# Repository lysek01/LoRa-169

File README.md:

# LoRa-169 Gateway Documentation

## Overview
The LoRa-169 Gateway is a Raspberry Pi-based system for receiving and transmitting LoRa packets on the 169 MHz IoT band using the SX127x radio module. It provides MQTT integration for remote control and configuration management.

## System Components

### 1. **lora_gateway.py** - Main Gateway Service
The core application that handles LoRa radio communication and MQTT integration.

**Features:**
- Continuous monitoring for incoming LoRa packets
- MQTT-based packet transmission (hex/ASCII formats)
- Dynamic configuration reloading without restart
- RSSI/SNR measurement and reporting
- Automatic radio recovery on errors

**MQTT Topics:**
- `loravsb/169/rx` - Published when packets are received
- `loravsb/169/tx/hex` - Subscribe to transmit hex-encoded data
- `loravsb/169/tx/ascii` - Subscribe to transmit ASCII data
- `loravsb/169/tx/ack` - Published transmission acknowledgments
- `loravsb/169/config/ack` - Published config change notifications

### 2. **lora_config.py** - Configuration Management Service
Shadow configuration service for remote MQTT-based configuration updates.

**MQTT Topics:**
- `loravsb/169/config/get` - Request current configuration
- `loravsb/169/config/set` - Update configuration (JSON payload)
- `loravsb/169/config/reported` - Reports current configuration state
- `loravsb/169/config/ack` - Configuration operation acknowledgments

### 3. **config.json** - Radio Configuration
LoRa radio parameters (frequency, spreading factor, bandwidth, coding rate, etc.)

### 4. **mqtt.conf** - MQTT Broker Configuration
MQTT connection settings (broker address, port, credentials). Edit this file with your actual broker settings before deployment.

### 5. **install.sh** - Installation Script
Automated setup script that installs dependencies and creates systemd services.

## Radio Configuration Parameters

| Parameter | Value | Description |
|-----------|-------|-------------|
| **frequency** | 169.4375 MHz | Operating frequency (169 MHz IoT band) |
| **spreading_factor** | 12 | SF12 (longest range, slowest speed) |
| **bandwidth** | 41.7 kHz | Narrow bandwidth for 169 MHz |
| **coding_rate** | 5 | 4/5 error correction |
| **ldro_enable** | true | Low Data Rate Optimization |
| **preamble_length** | 8 | 8-symbol preamble |
| **sync_word** | 18 (0x12) | Network sync word |
| **crc_enable** | true | CRC error checking enabled |
| **tx_power** | 30 | 30 dBm output power |
| **rx_gain** | "G1" | Boosted LNA gain mode |

## Error Messages and Status Codes

### Configuration Service Status Codes (lora_config.py)

| Code | Constant | Description | Trigger |
|------|----------|-------------|---------|
| **11** | REPORTED_SENT | Configuration successfully reported | After MQTT connect or GET request |
| **12** | CONFIG_OVERWRITTEN | Configuration file updated | Successful SET operation |
| **13** | CONFIG_APPLIED | New configuration applied to radio | Config change detected |
| **14** | INVALID_PAYLOAD | Malformed JSON received | Invalid/empty JSON in SET message |
| **15** | WRITE_FAILED | File write error | Cannot write config.json |
| **16** | INTERNAL_ERROR | Unhandled exception | Unexpected error in handler |

### Gateway Radio Status Codes (lora_gateway.py)

| Code | Constant | Description |
|------|----------|-------------|
| **0** | STATUS_DEFAULT | Default/idle state |
| **1** | STATUS_TX_WAIT | Waiting for transmission |
| **2** | STATUS_TX_TIMEOUT | Transmission timeout |
| **3** | STATUS_TX_DONE | Transmission completed successfully |
| **4** | STATUS_RX_WAIT | Waiting to receive |
| **5** | STATUS_RX_CONTINUOUS | Continuous receive mode active |
| **6** | STATUS_RX_TIMEOUT | Reception timeout |
| **7** | STATUS_RX_DONE | Packet received successfully |
| **8** | STATUS_HEADER_ERR | LoRa header corruption detected |
| **9** | STATUS_CRC_ERR | CRC checksum validation failed |
| **10** | STATUS_CAD_WAIT | Channel Activity Detection in progress |
| **11** | STATUS_CAD_DETECTED | Channel activity detected |
| **12** | STATUS_CAD_DONE | CAD completed |

### Error Messages

| Error Message | Location | Meaning | Resolution |
|---------------|----------|---------|------------|
| "Invalid JSON payload" | lora_config.py:103 | SET message contains non-JSON data | Send valid JSON object |
| "Write failed" | lora_config.py:112 | Cannot write config.json to disk | Check file permissions |
| "payload must be non-empty JSON object" | lora_config.py:101 | Empty or invalid config object | Provide valid configuration |
| "Unhandled error" | lora_config.py:120 | Unexpected exception occurred | Check system logs |
| "Run as root: sudo bash $0" | install.sh:20 | Installation requires root privileges | Run with sudo |
| "Script not found: {path}" | install.sh:43-44 | Required Python script missing | Verify file structure |

## Installation

### 1. Configure MQTT Connection

Before running the installation, edit the MQTT configuration file with your broker settings:

```bash
cd /path/to/gateway
nano mqtt.conf
```

Configure your MQTT broker settings:
```ini
# MQTT Broker Configuration
MQTT_BROKER=192.168.1.100    # Your MQTT broker IP/hostname
MQTT_PORT=1883                # MQTT port (usually 1883)
MQTT_USERNAME=your_username   # MQTT username (optional)
MQTT_PASSWORD=your_password   # MQTT password (optional)
```

**Required parameters:**
- `MQTT_BROKER` - Broker IP address or hostname
- `MQTT_PORT` - Broker port number

**Optional parameters:**
- `MQTT_USERNAME` - Username for authentication
- `MQTT_PASSWORD` - Password for authentication

**Important:** The repository contains `mqtt.conf` with example values. Edit this file with your actual broker credentials before deployment.

### 2. Run Installation Script

```bash
sudo bash install.sh
```

The script will:
1. Install system dependencies (Python3, venv, git)
2. Create Python virtual environment
3. Install Python packages from requirements.txt
4. Create two systemd services
5. Enable and start services

**Services Created:**
- `loravsb-gateway.service` - Main gateway service
- `loravsb-config.service` - Configuration manager service

**Service Features:**
- **Auto-restart on failure** - Services restart automatically if they crash
- **Boot timeout protection** - 10s timeout for LoRa module initialization
- **Start limit protection** - Max 3 restart attempts per minute (gateway), 5 attempts (config)
- **Proper GPIO initialization** - RST pin set to known state before module init

## Hardware Requirements

- **Platform:** Raspberry Pi (tested on Pi 3/4)
- **Radio Module:** SX127x LoRa transceiver
- **Connections:**
  - SPI Bus 0, CS 0
  - GPIO 25: Reset pin
  - GPIO 5: DIO0 interrupt pin

## Usage Examples

### Transmit Hex Data via MQTT
```bash
mosquitto_pub -h 158.196.109.41 -t loravsb/169/tx/hex -m "48656C6C6F"
```

### Transmit ASCII Data
```bash
mosquitto_pub -h 158.196.109.41 -t loravsb/169/tx/ascii -m "Hello"
```

### Update Configuration
```bash
mosquitto_pub -h 158.196.109.41 -t loravsb/169/config/set -m '{"spreading_factor":11}'
```

### Request Current Configuration
```bash
mosquitto_pub -h 158.196.109.41 -t loravsb/169/config/get -m ""
```

### Subscribe to Received Packets
```bash
mosquitto_sub -h 158.196.109.41 -t loravsb/169/rx
```

## Service Management

### Check Service Status
```bash
sudo systemctl status loravsb-gateway
sudo systemctl status loravsb-config
```

### View Logs
```bash
sudo journalctl -u loravsb-gateway -f
sudo journalctl -u loravsb-config -f
```

### Restart Services
```bash
sudo systemctl restart loravsb-gateway
sudo systemctl restart loravsb-config
```

### Stop Services
```bash
sudo systemctl stop loravsb-gateway
sudo systemctl stop loravsb-config
```

### Disable Auto-Start
```bash
sudo systemctl disable loravsb-gateway
sudo systemctl disable loravsb-config
```

## Architecture Details

### File Structure
```
gateway/
├── config.json              # Radio configuration (LoRa parameters)
├── mqtt.conf                # MQTT broker configuration (edit before install)
├── lora_gateway.py          # Main gateway service
├── lora_config.py           # Config management service
├── install.sh               # Installation script
├── requirements.txt         # Python dependencies
```

### Main Gateway Service Flow
1. Load MQTT configuration from mqtt.conf
2. Load radio configuration from config.json
3. Initialize GPIO (set RST pin to known state)
4. Initialize SX127x radio via SPI with timeout/retry logic
5. Connect to MQTT broker
6. Enter main loop:
   - Check for configuration changes (reload if needed)
   - Check for received LoRa packets
   - Process pending transmissions
   - Handle MQTT messages

### Configuration Service Flow
1. Load MQTT configuration from mqtt.conf
2. Connect to MQTT broker
3. Subscribe to config GET/SET topics
4. Publish initial configuration state
5. Wait for incoming messages:
   - **GET**: Publish current config.json
   - **SET**: Merge changes into config.json atomically

### MQTT Message Flow

**Receiving LoRa Packet:**
```
LoRa Radio → lora_gateway.py → MQTT Publish → loravsb/169/rx
```

**Transmitting LoRa Packet:**
```
MQTT Subscribe → loravsb/169/tx/hex → lora_gateway.py → LoRa Radio
```

**Configuration Update:**
```
MQTT → loravsb/169/config/set → lora_config.py → config.json
→ lora_gateway.py (detects change) → Reload radio
```

## Dependencies

### Python Packages (requirements.txt)
- **RPi.GPIO** - Raspberry Pi GPIO library
- **spidev** - SPI device interface
- **paho-mqtt>=2.0,<3** - MQTT client library
- **LoRaRF** - LoRa radio driver for SX127x
- **wheel** - Python package wheel format
- **setuptools** - Python package tools

### System Requirements
- Debian/Ubuntu-based Linux distribution
- Python 3.7+
- systemd init system
- Root/sudo access for installation

## Troubleshooting

### Gateway Not Starting
**Symptoms:** Service fails to start or crashes immediately

**Common Error Messages:**
- `RuntimeError: MQTT config file not found: mqtt.conf` - Missing MQTT configuration
- `RuntimeError: Missing required MQTT config keys: broker` - Invalid mqtt.conf
- `RuntimeError: Failed to initialize module` - LoRa module not responding

**Possible Causes:**
1. **Missing mqtt.conf** - MQTT configuration file doesn't exist
2. **Invalid mqtt.conf** - Missing required keys (MQTT_BROKER, MQTT_PORT)
3. **LoRa module not responding** - Hardware issue or timing problem
4. **SPI interface not enabled** - Raspberry Pi SPI disabled
5. **Incorrect GPIO pin connections** - Wrong wiring
6. **Missing dependencies** - Python packages not installed

**Solutions:**
```bash
# 1. Check and edit mqtt.conf
nano /path/to/gateway/mqtt.conf

# 2. Verify mqtt.conf has required keys
cat mqtt.conf | grep -E "MQTT_BROKER|MQTT_PORT"

# 3. Check service logs for detailed error
sudo journalctl -u loravsb-gateway -n 50

# 4. Enable SPI on Raspberry Pi
sudo raspi-config
# Navigate to: Interface Options → SPI → Enable

# 5. Verify Python dependencies
source venv/bin/activate
pip list | grep -E "LoRaRF|paho-mqtt|RPi.GPIO"

# 6. Test LoRa module manually
python3 -c "from LoRaRF import SX127x; import time; l = SX127x(); l.setSpi(0,0,1000000); l.setPins(25,5); time.sleep(0.1); print('OK' if l.begin() else 'FAIL')"
```

### No Packets Received
**Symptoms:** Gateway running but no packets appear on MQTT

**Possible Causes:**
1. Incorrect frequency or radio parameters
2. No transmitter in range
3. Antenna not connected
4. Radio module hardware failure

**Solutions:**
```bash
# Check current configuration
mosquitto_pub -h 158.196.109.41 -t loravsb/169/config/get -m ""
mosquitto_sub -h 158.196.109.41 -t loravsb/169/config/reported -C 1

# Verify radio parameters match transmitter
cat /opt/loravsb/config.json

# Check service logs for errors
sudo journalctl -u loravsb-gateway -f
```

### Configuration Not Applying
**Symptoms:** SET commands sent but configuration unchanged

**Possible Causes:**
1. Config service not running
2. Invalid JSON payload
3. File write permissions
4. MQTT connection issues

**Solutions:**
```bash
# Check config service status
sudo systemctl status loravsb-config

# View config service logs
sudo journalctl -u loravsb-config -n 50

# Test configuration update
mosquitto_pub -h 158.196.109.41 -t loravsb/169/config/set -m '{"spreading_factor":11}'

# Check for acknowledgment
mosquitto_sub -h 158.196.109.41 -t loravsb/169/config/ack -C 1
```

### MQTT Connection Failed
**Symptoms:** Cannot connect to MQTT broker

**Possible Causes:**
1. Incorrect broker IP address
2. Network connectivity issues
3. Firewall blocking port 1883
4. Invalid credentials

**Solutions:**
```bash
# Test MQTT connectivity
mosquitto_pub -h 158.196.109.41 -p 1883 -t test -m "hello"

# Check network connectivity
ping 158.196.109.41

# Verify port is open
nc -zv 158.196.109.41 1883

# Check credentials in source code
grep MQTT_USERNAME /opt/loravsb/lora_gateway.py
```

## Future Improvements

### Recommended Enhancements
1. **Security:**
   - Environment variable-based configuration
   - TLS/SSL support for MQTT
   - Authentication token validation

2. **Reliability:**
   - Structured logging with log levels
   - Health check endpoint
   - Watchdog timer for radio hang detection
   - Automatic radio reset on persistent errors

3. **Monitoring:**
   - Prometheus metrics export
   - Packet statistics (RX/TX counters, error rates)
   - RSSI/SNR histograms

4. **Code Quality:**
   - Unit test suite
   - Class-based architecture (replace globals)
   - Docstrings for all functions
   - Type hints (Python 3.7+)

5. **Features:**
   - Multiple radio support
   - Packet filtering/routing
   - Time-scheduled transmissions
   - Over-the-air configuration

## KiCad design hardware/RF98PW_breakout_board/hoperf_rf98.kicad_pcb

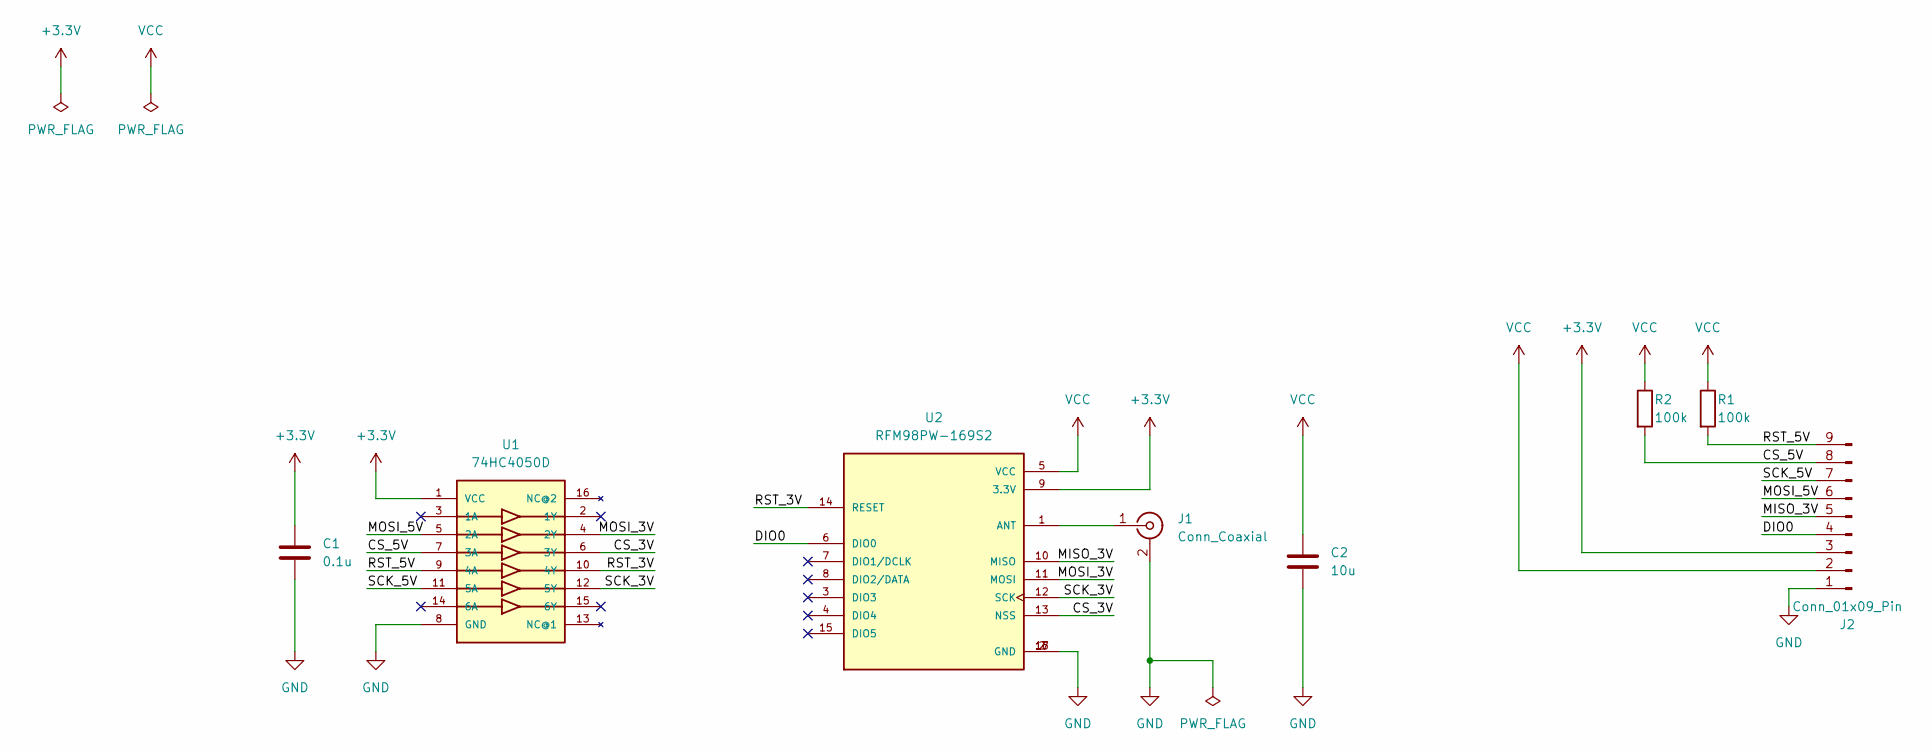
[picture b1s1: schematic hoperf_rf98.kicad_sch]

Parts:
C1: 0.1u; C_0805_2012Metric
C2: 10u; C_0805_2012Metric
J1: Conn_Coaxial; SMA_Amphenol_901-143_Horizontal
J2: Conn_01x09_Pin; PinHeader_1x09_P2.54mm_Vertical
R1, R2: 100k; R_0805_2012Metric
U1: 74HC4050D; SO16
U2: RFM98PW-169S2; XCVR_RFM98PW-169S2; PARTREV 1.1

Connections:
+3.3V: C1.2, J2.3, U1.1 (VCC), U2.9 (3.3V)
/CS_3V: U1.6 (3Y), U2.13 (NSS)
/CS_5V: J2.8, R2.2, U1.7 (3A)
/DIO0: J2.4, U2.6 (DIO0)
/MISO_3V: J2.5, U2.10 (MISO)
/MOSI_3V: U1.4 (2Y), U2.11 (MOSI)
/MOSI_5V: J2.6, U1.5 (2A)
/RST_3V: U1.10 (4Y), U2.14 (RESET)
/RST_5V: J2.9, R1.2, U1.9 (4A)
/SCK_3V: U1.12 (5Y), U2.12 (SCK)
/SCK_5V: J2.7, U1.11 (5A)
GND: C1.1, C2.1, J1.2 (Ext), J2.1, U1.8 (GND), U2.2 (GND), U2.16 (GND), U2.17 (GND)
unnamed: J1.1 (In), U2.1 (ANT)
VCC: C2.2, J2.2, R1.1, R2.1, U2.5 (VCC)

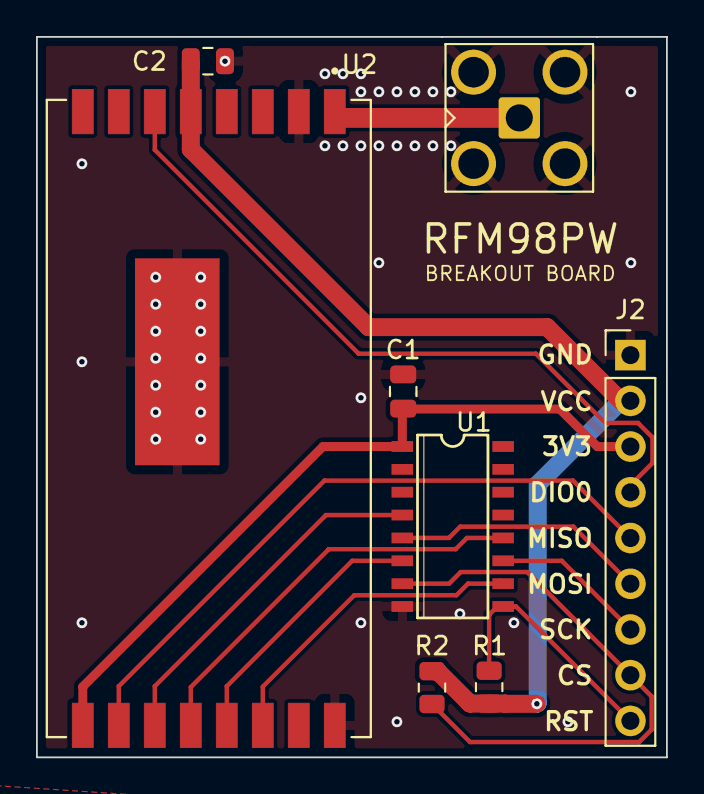
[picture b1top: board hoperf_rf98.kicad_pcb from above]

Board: 2 copper layers, 35.0 x 40.0 mm, 8 parts (0 on the bottom side), 14 nets.

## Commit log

2025-10-21 minor update #2
2025-10-22 Easy install
2025-10-22 Easy install update
2025-10-29 Arduino update
2025-11-22 reboot fix
2025-11-23 boot floating pin fix
2026-01-06 looping fix test
2026-01-07 fix continus rx
2026-01-07 add loop protection
2026-01-13 add logging
2026-01-13 more readable code
2026-01-15 watchdog
2026-01-15 ignore reatined messages
